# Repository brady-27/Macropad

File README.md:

# Macropad
A small macropad to get comfortable with 3d design, cad, printing, and pcb design
The main goal of this macropad is to make a device that I can easily access physically to control media like spotify. I plan to make a pad with 3 keyboard switched, a rotary encoder, and and small led screen. 
The 3 keys are going to be [Previous] / [Pause/Resume] / [Skip] 

What its ging to be able to do
1. Display Sonng Title and Artist + potentially album or song voer
2. play/resume
3. skip
4. back
5. volume control

So thedevlog shows only a basic 3 key macropad but I did some changes cause I had a change in heart so thats why I have a different macropad than shown in devlog and I forgot to log my time so I couldnt post a devlog.

Screen Shot of my schematic and PCB

Screen Shot of my Case

Screen Shot of my BOM

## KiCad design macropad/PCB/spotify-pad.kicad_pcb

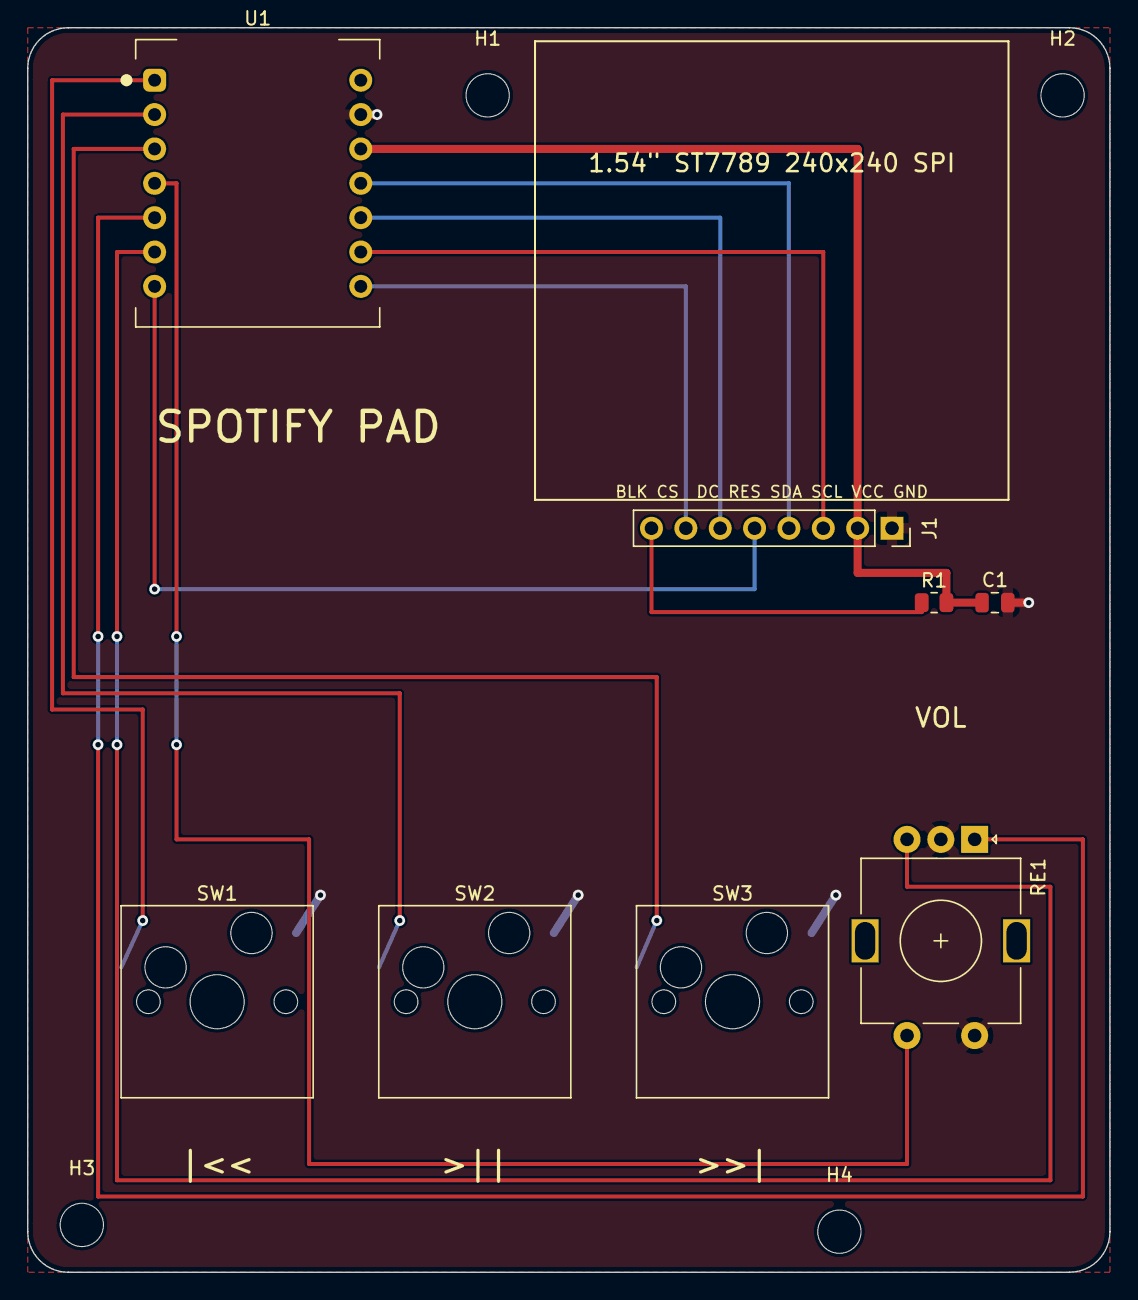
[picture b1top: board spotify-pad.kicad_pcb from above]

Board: 2 copper layers, 80.0 x 92.0 mm, 12 parts (0 on the bottom side), 14 nets.

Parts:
C1: 10uF; C_0805_2012Metric
H1, H2, H3, H4: M3; MountingHole_3.2mm_M3
J1: LCD_1.54in_ST7789; PinSocket_1x08_P2.54mm_Vertical
R1: 0R; R_0805_2012Metric
RE1: EC11; RotaryEncoder_Alps_EC11E-Switch_Vertical_H20mm
SW1, SW2, SW3: MX_HOTSWAP; SW_Hotswap_Kailh_MX
U1: XIAO-RP2040; XIAO-RP2040-DIP

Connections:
+3V3: C1.1, J1.2, R1.2, U1.12
ENC_A: RE1.A, U1.5
ENC_B: RE1.B, U1.6
ENC_SW: RE1.S1, U1.4
GND: C1.2, J1.1, RE1.C, RE1.S2, SW1.2, SW2.2, SW3.2, U1.13
LCD_BL: J1.8, R1.1
LCD_CS: J1.7, U1.8
LCD_DC: J1.6, U1.10
LCD_MOSI: J1.4, U1.11
LCD_RST: J1.5, U1.7
LCD_SCK: J1.3, U1.9
SW_BACK: SW1.1, U1.1
SW_NEXT: SW3.1, U1.3
SW_PLAY: SW2.1, U1.2

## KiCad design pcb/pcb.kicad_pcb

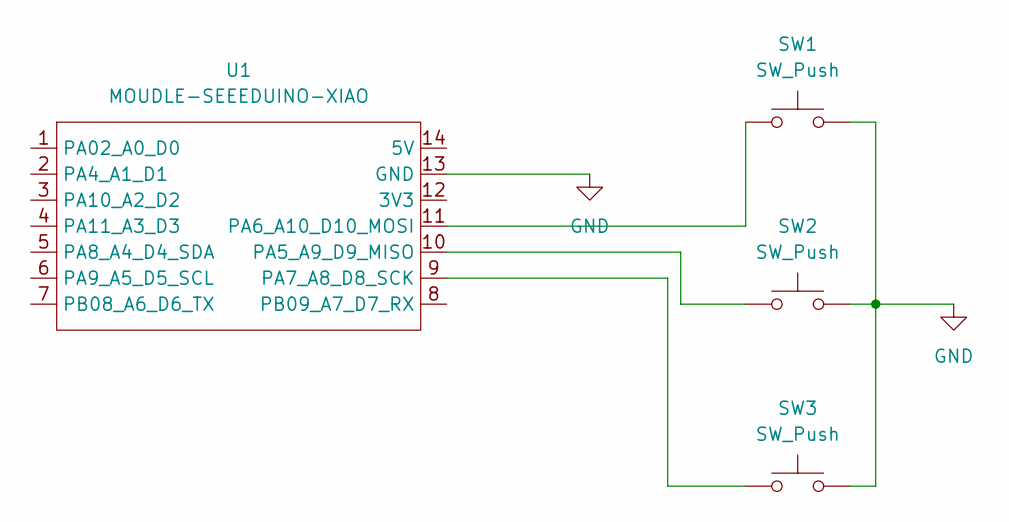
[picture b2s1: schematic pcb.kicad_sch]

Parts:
SW1, SW2, SW3: SW_Push; SW_Cherry_MX_1.00u_PCB
U1: MOUDLE-SEEEDUINO-XIAO; XIAO-Generic-Hybrid-14P-2.54-21X17.8MM

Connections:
GND: SW1.2, SW2.2, SW3.2, U1.13 (GND)
unnamed: SW2.1, U1.10 (PA5_A9_D9_MISO)
unnamed: SW1.1, U1.11 (PA6_A10_D10_MOSI)
unnamed: SW3.1, U1.9 (PA7_A8_D8_SCK)

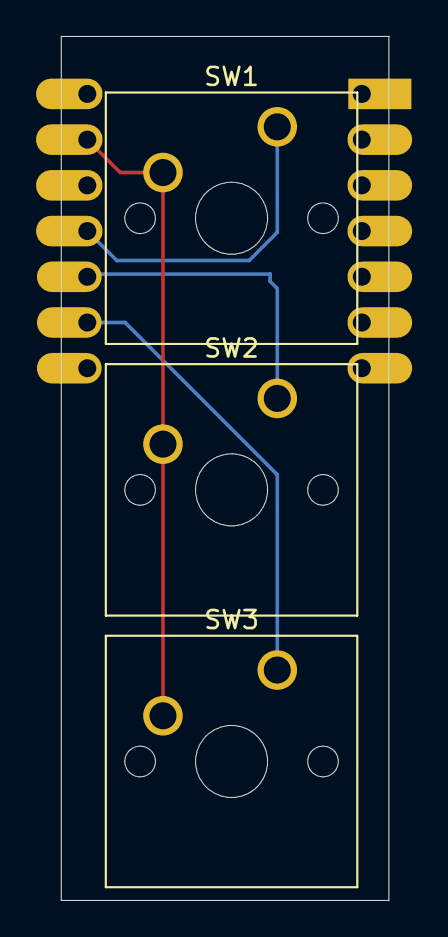
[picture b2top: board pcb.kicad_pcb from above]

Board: 2 copper layers, 18.2 x 48.0 mm, 4 parts (1 on the bottom side), 4 nets.

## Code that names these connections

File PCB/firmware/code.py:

# Spotify Pad — CircuitPython firmware for Seeed XIAO RP2040
#
# Keys send USB media keys (work with Spotify or any player, no host app needed).
# The display listens on USB serial for song info + cover art pushed by the
# companion script host/spotify_display.py running on your computer.
#
# Setup:
#   1. Flash CircuitPython for XIAO RP2040 (circuitpython.org/board/seeeduino_xiao_rp2040)
#   2. Copy this file to CIRCUITPY/code.py
#   3. Copy adafruit_hid + adafruit_st7789 + adafruit_display_text libs to CIRCUITPY/lib
#
import time
import board
import busio
import digitalio
import rotaryio
import displayio
import usb_cdc
import usb_hid
from adafruit_hid.consumer_control import ConsumerControl
from adafruit_hid.consumer_control_code import ConsumerControlCode

try:
    from fourwire import FourWire          # CircuitPython 9+
except ImportError:
    from displayio import FourWire         # CircuitPython 8

from adafruit_st7789 import ST7789
from adafruit_display_text import label as text_label
import terminalio

# ---------------- pins (match PCB) ----------------
PIN_SW_BACK = board.D0
PIN_SW_PLAY = board.D1
PIN_SW_NEXT = board.D2
PIN_ENC_SW = board.D3
PIN_ENC_EAST = board.D4    # encoder channel A (east pad)
PIN_ENC_WEST = board.D5    # encoder channel B (west pad)
PIN_LCD_RST = board.D6
PIN_LCD_CS = board.D7
PIN_LCD_SCK = board.D8
PIN_LCD_DC = board.D9
PIN_LCD_MOSI = board.D10

# ---------------- display ----------------
displayio.release_displays()
spi = busio.SPI(clock=PIN_LCD_SCK, MOSI=PIN_LCD_MOSI)
bus = FourWire(spi, command=PIN_LCD_DC, chip_select=PIN_LCD_CS, reset=PIN_LCD_RST)
display = ST7789(bus, width=240, height=240, rowstart=80, rotation=0)

root = displayio.Group()
display.root_group = root

cover_bitmap = displayio.Bitmap(160, 160, 65536)
cover_shader = displayio.ColorConverter(input_colorspace=displayio.Colorspace.RGB565)
cover_tile = displayio.TileGrid(cover_bitmap, pixel_shader=cover_shader, x=40, y=8)
root.append(cover_tile)

song_lbl = text_label.Label(terminalio.FONT, text="Spotify Pad", color=0xFFFFFF, x=8, y=185, scale=2)
artist_lbl = text_label.Label(terminalio.FONT, text="waiting for host...", color=0x1DB954, x=8, y=215, scale=1)
root.append(song_lbl)
root.append(artist_lbl)

# ---------------- inputs ----------------
cc = ConsumerControl(usb_hid.devices)

def make_button(pin):
    b = digitalio.DigitalInOut(pin)
    b.direction = digitalio.Direction.INPUT
    b.pull = digitalio.Pull.UP
    return b

btn_back = make_button(PIN_SW_BACK)
btn_play = make_button(PIN_SW_PLAY)
btn_next = make_button(PIN_SW_NEXT)
btn_mute = make_button(PIN_ENC_SW)
encoder = rotaryio.IncrementalEncoder(PIN_ENC_EAST, PIN_ENC_WEST)

last_pos = encoder.position
prev = {"back": True, "play": True, "next": True, "mute": True}

# ---------------- serial protocol ----------------
# Host sends lines over the data serial port:
#   TXT|<song title>|<artist>\n
#   IMG|<len>\n  followed by <len> raw RGB565 big-endian bytes (160x160)
ser = usb_cdc.data

def poll_serial():
    if ser is None or ser.in_waiting == 0:
        return
    line = ser.readline()
    if not line:
        return
    try:
        line = line.decode().strip()
    except UnicodeError:
        return
    if line.startswith("TXT|"):
        parts = line.split("|")
        if len(parts) >= 3:
            song_lbl.text = parts[1][:18]
            artist_lbl.text = parts[2][:38]
    elif line.startswith("IMG|"):
        try:
            n = int(line.split("|")[1])
        except (IndexError, ValueError):
            return
        buf = bytearray(n)
        mv = memoryview(buf)
        got = 0
        deadline = time.monotonic() + 5
        while got < n and time.monotonic() < deadline:
            if ser.in_waiting:
                got += ser.readinto(mv[got:])
        if got == n:
            idx = 0
            for y in range(160):
                for x in range(160):
                    cover_bitmap[x, y] = (buf[idx] << 8) | buf[idx + 1]
                    idx += 2

while True:
    # buttons (active low)
    for name, btn, code in (
        ("back", btn_back, ConsumerControlCode.SCAN_PREVIOUS_TRACK),
        ("play", btn_play, ConsumerControlCode.PLAY_PAUSE),
        ("next", btn_next, ConsumerControlCode.SCAN_NEXT_TRACK),
        ("mute", btn_mute, ConsumerControlCode.MUTE),
    ):
        pressed = not btn.value
        if pressed and prev[name]:
            cc.send(code)
        prev[name] = pressed

    # encoder -> volume
    pos = encoder.position
    while pos > last_pos:
        cc.send(ConsumerControlCode.VOLUME_INCREMENT)
        last_pos += 1
    while pos < last_pos:
        cc.send(ConsumerControlCode.VOLUME_DECREMENT)
        last_pos -= 1

    poll_serial()
    time.sleep(0.005)
